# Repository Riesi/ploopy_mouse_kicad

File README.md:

# DISCLAIMER
## How was this ported to KiCAD?

The heavy lifting was done by the [altium2kicad](https://github.com/thesourcerer8/altium2kicad) converter. If you like this port do consider donating to the converter project!

After that I took the converted files and pruned unnecessary ones. Then I fixed the schematics by replacing the broken symbols with either existing ones or created custom symbols.
All components have been named as they appear in the PCB to allow for relinking of the footprints with the `Update Schematic from PCB` option in eeschema.
Finally I fixed the DRC errors generated in the PCB (default design rule settings). This meant fixing the broken edge cut lines, due to the converter creating non closed and not fully connected lines. It also sprinkled some edge cut dots over the lines, which was not that easy to find!

### Can I use this port instead of the main project?

I don't think anything speaks against using this KiCAD version. But be warned that I haven't produced a PCB with it myself! So things could be broken!
If you just want a working PCB you should use Gerber files produced from the original version instead.

If you want to help verifying the design please do so!

### Current Validation

Validation has been done with the `Gerbv` tool, which allows to compare two Gerber files and show their difference/overlap.
The files used for the validation are located in `./gerber_diff_view`. You can run the `diff_gerber.sh` to verify some of the Gerber files yourself. Be sure to generate the KiCAD Gerber in the following path `hardware/electronics/QMKMouse/gerber/` before running the script. There are also comparison shots of some layers in which the white corresponds to KiCAD, green to Altium and purple to the matching XOR of both.

#### Labels:

Text is different due to fonts.
Drawings look correct.

#### Layers:

Only minimal difference due to difference in clearance to the border cut and filling algorithm.
KiCAD version has a bit more portions filled. This should not be an issue.

#### Edge Cuts:

Match.

#### Drill:
Drill holes look correct.
Mismatch on some holes that are not plated in the fabricated PCB, but Altium files still contain them as plated.
Should be no problem.

#### Drill Maps:
No drill mapped to optical sensor in KiCAD, but this should not be an issue.

#### Masks:

Match.

#### Pastes:

Match.

# The Ploopy Mouse

By some stroke of luck, you've made your way here. The Ploopy Mouse. Your life will never be the same.

This repository contains all of the design and production files necessary to make a Ploopy Mouse. We've also included some kick-ass documentation in the Wiki on how to get it made, assemble it, and program it.

What are you waiting for? Your new life awaits.

## QMK?!

Kits bought from the [Ploopy store](https://ploopy.co/product-category/mouse/) come with QMK preloaded. Check out the Wiki for instructions on how to load new firmware onto your device. (It's super easy!)

The firmware hex file that ships with all Mice is included in this repository as well, as `ploopyco_mouse_via.hex`. The hex was built with QMK version 0.11.1.

## Under what license is this released?

Everything in this repository is released under OHL CERN v2-S. Check the LICENSE.md file for full license text.

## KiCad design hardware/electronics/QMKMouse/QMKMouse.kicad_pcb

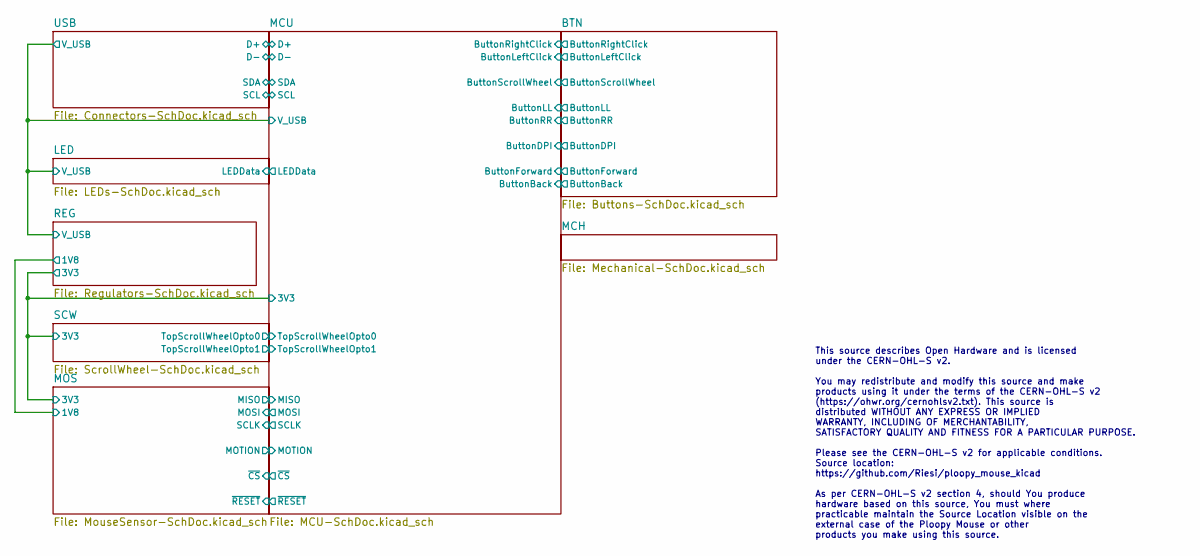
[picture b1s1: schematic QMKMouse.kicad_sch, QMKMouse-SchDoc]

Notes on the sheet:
This source describes Open Hardware and is licensed under the CERN-OHL-S v2. You may redistribute and modify this source and make products using it under the terms of the CERN-OHL-S v2 (https://ohwr.org/cernohlsv2.txt). This source is distributed WITHOUT ANY EXPRESS OR IMPLIED WARRANTY, INCLUDING O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

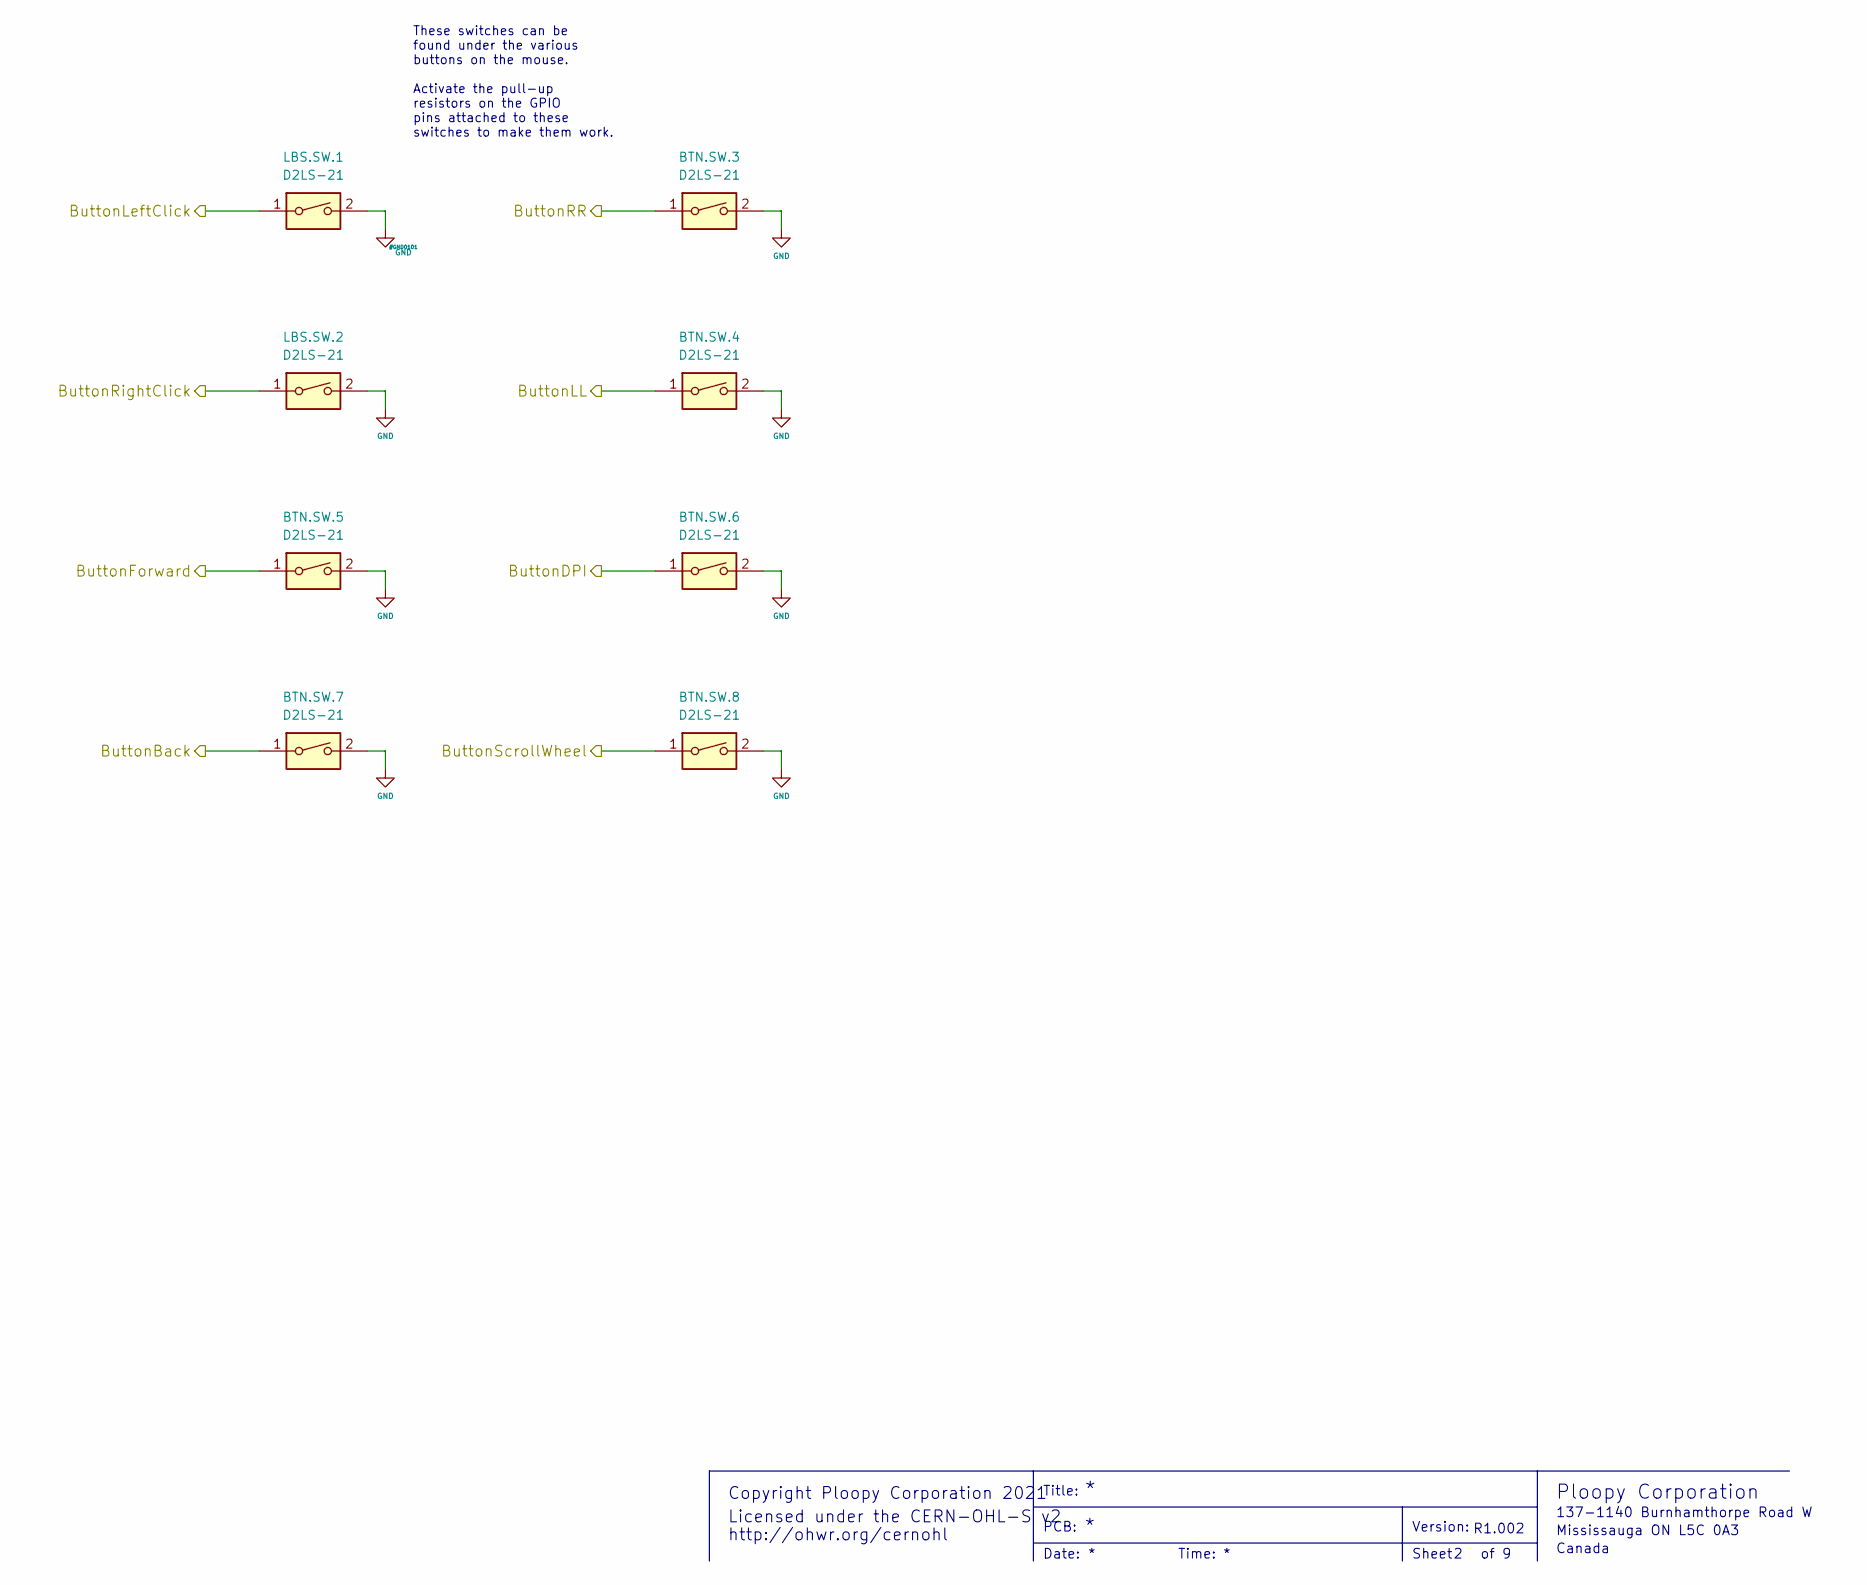
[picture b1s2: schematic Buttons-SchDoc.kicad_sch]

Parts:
BTN.SW.3, BTN.SW.4, BTN.SW.5, BTN.SW.6, BTN.SW.7, BTN.SW.8: D2LS-21
LBS.SW.1, LBS.SW.2: D2LS-21

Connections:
/BTN/ButtonBack: BTN.SW.7.1; also elsewhere on the board
/BTN/ButtonDPI: BTN.SW.6.1; also elsewhere on the board
/BTN/ButtonForward: BTN.SW.5.1; also elsewhere on the board
/BTN/ButtonLL: BTN.SW.4.1; also elsewhere on the board
/BTN/ButtonLeftClick: LBS.SW.1.1; also elsewhere on the board
/BTN/ButtonRR: BTN.SW.3.1; also elsewhere on the board
/BTN/ButtonRightClick: LBS.SW.2.1; also elsewhere on the board
/BTN/ButtonScrollWheel: BTN.SW.8.1; also elsewhere on the board
GND: BTN.SW.3.2, BTN.SW.4.2, BTN.SW.5.2, BTN.SW.6.2, BTN.SW.7.2, BTN.SW.8.2, LBS.SW.1.2, LBS.SW.2.2; also elsewhere on the board

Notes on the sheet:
Canada
PCB:
137-1140 Burnhamthorpe Road W
http://ohwr.org/cernohl
Copyright Ploopy Corporation 2021
Sheet
Title:
Mississauga ON L5C 0A3
These switches can be found under the various buttons on the mouse. Activate the pull-up resistors on the GPIO pins attached to these switches to make them work.
Version:
Ploopy Corporation
Licensed under the CERN-OHL-S v2
Time:
Date:
R1.002

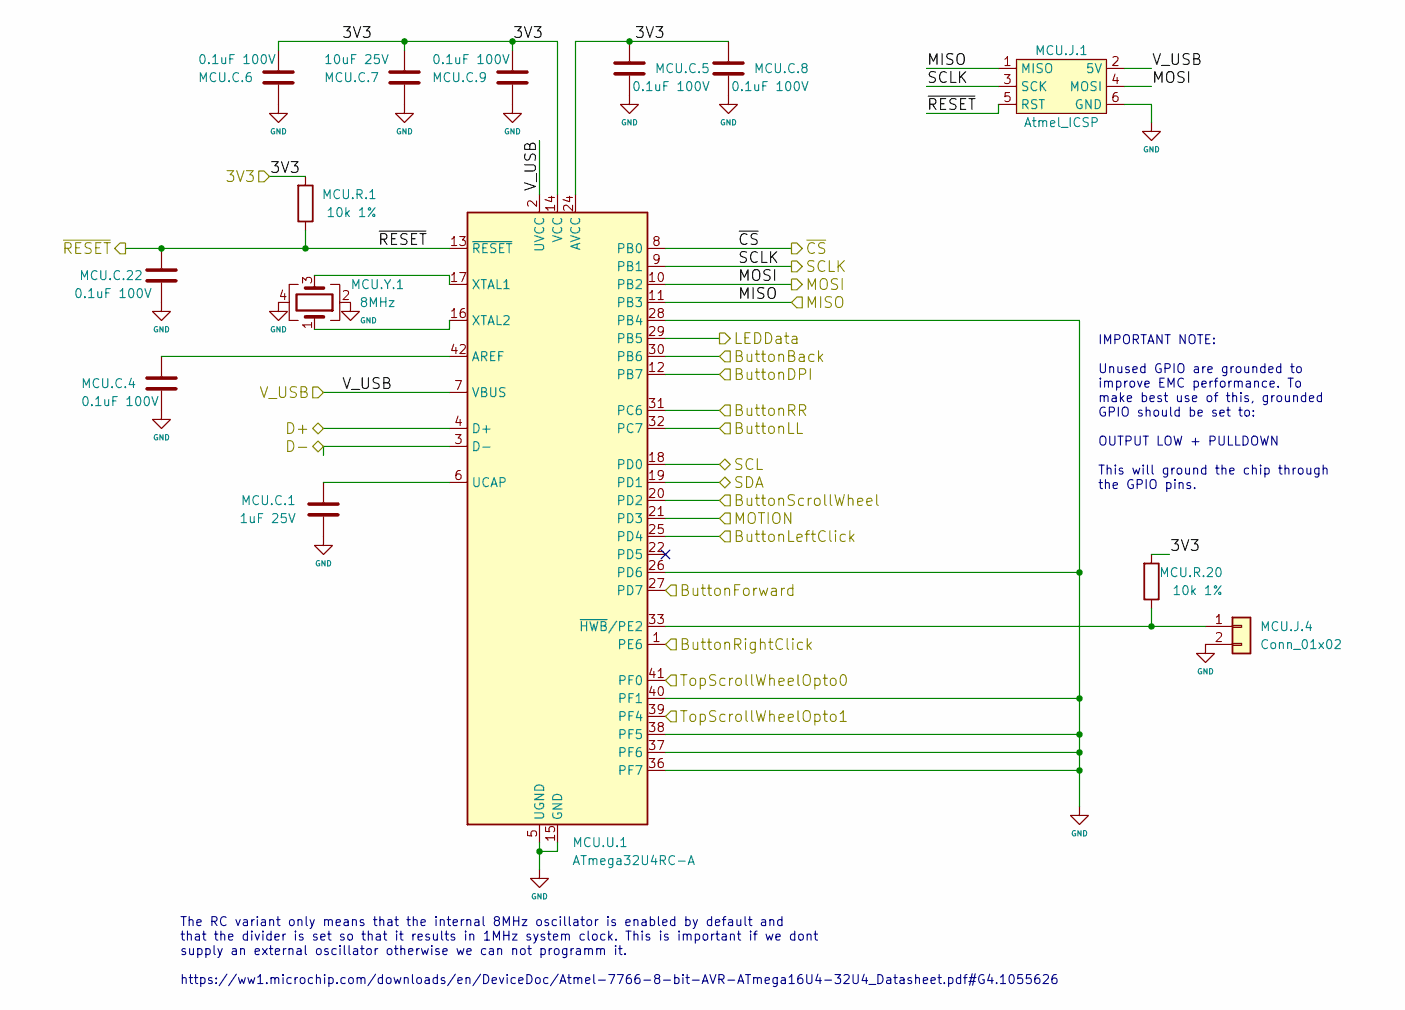
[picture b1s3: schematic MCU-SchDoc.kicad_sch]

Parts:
MCU.C.1: 1uF 25V; C_0805
MCU.C.4, MCU.C.5, MCU.C.6, MCU.C.8, MCU.C.9, MCU.C.22: 0.1uF 100V; C_0805
MCU.C.7: 10uF 25V; C_0805
MCU.J.1: Atmel_ICSP; 6x2
MCU.J.4: Conn_01x02; 2x1
MCU.R.1, MCU.R.20: 10k 1%; 0805
MCU.U.1: ATmega32U4RC-A; ATMEGA32U4 - TQFP80P1200X1200X120-44N
MCU.Y.1: 8MHz; LFXTAL055663BULK

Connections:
/BTN/ButtonBack: MCU.U.1.30 (PB6); also elsewhere on the board
/BTN/ButtonDPI: MCU.U.1.12 (PB7); also elsewhere on the board
/BTN/ButtonForward: MCU.U.1.27 (PD7); also elsewhere on the board
/BTN/ButtonLL: MCU.U.1.32 (PC7); also elsewhere on the board
/BTN/ButtonLeftClick: MCU.U.1.25 (PD4); also elsewhere on the board
/BTN/ButtonRR: MCU.U.1.31 (PC6); also elsewhere on the board
/BTN/ButtonRightClick: MCU.U.1.1 (PE6); also elsewhere on the board
/BTN/ButtonScrollWheel: MCU.U.1.20 (PD2); also elsewhere on the board
/LED/LEDData: MCU.U.1.29 (PB5); also elsewhere on the board
/LED/V_USB: MCU.J.1.2 (5V), MCU.U.1.2 (UVCC), MCU.U.1.7 (VBUS); also elsewhere on the board
/MCU/3V3: MCU.C.5.2, MCU.C.6.2, MCU.C.7.2, MCU.C.8.2, MCU.C.9.2, MCU.R.1.2, MCU.R.20.2, MCU.U.1.14 (VCC), MCU.U.1.24 (AVCC), MCU.U.1.34 (VCC), MCU.U.1.44 (AVCC); also elsewhere on the board
/MCU/D+: MCU.U.1.4 (D+); also elsewhere on the board
/MCU/D-: MCU.U.1.3 (D-); also elsewhere on the board
/MCU/MISO: MCU.J.1.1 (MISO), MCU.U.1.11 (PB3); also elsewhere on the board
/MCU/MOSI: MCU.J.1.4 (MOSI), MCU.U.1.10 (PB2); also elsewhere on the board
/MCU/MOTION: MCU.U.1.21 (PD3); also elsewhere on the board
/MCU/SCL: MCU.U.1.18 (PD0); also elsewhere on the board
/MCU/SCLK: MCU.J.1.3 (SCK), MCU.U.1.9 (PB1); also elsewhere on the board
/MCU/SDA: MCU.U.1.19 (PD1); also elsewhere on the board
/MCU/TopScrollWheelOpto0: MCU.U.1.41 (PF0); also elsewhere on the board
/MCU/TopScrollWheelOpto1: MCU.U.1.39 (PF4); also elsewhere on the board
/MCU/~CS: MCU.U.1.8 (PB0); also elsewhere on the board
/MCU/~RESET: MCU.C.22.2, MCU.J.1.5 (RST), MCU.R.1.1, MCU.U.1.13 (~RESET); also elsewhere on the board
GND: MCU.C.1.1, MCU.C.4.1, MCU.C.5.1, MCU.C.6.1, MCU.C.7.1, MCU.C.8.1, MCU.C.9.1, MCU.C.22.1, MCU.J.1.6 (GND), MCU.J.4.2, MCU.U.1.5 (UGND), MCU.U.1.15 (GND), MCU.U.1.23 (GND), MCU.U.1.26 (PD6), MCU.U.1.28 (PB4), MCU.U.1.35 (GND), MCU.U.1.36 (PF7), MCU.U.1.37 (PF6), MCU.U.1.38 (PF5), MCU.U.1.40 (PF1), MCU.U.1.43 (GND), MCU.Y.1.2, MCU.Y.1.4; also elsewhere on the board
unnamed: MCU.C.1.2, MCU.U.1.6 (UCAP)
unnamed: MCU.C.4.2, MCU.U.1.42 (AREF)
unnamed: MCU.J.4.1, MCU.R.20.1, MCU.U.1.33 (~HWB/PE2)
unnamed: MCU.U.1.16 (XTAL2), MCU.Y.1.1
unnamed: MCU.U.1.17 (XTAL1), MCU.Y.1.3

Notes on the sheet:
The RC variant only means that the internal 8MHz oscillator is enabled by default and that the divider is set so that it results in 1MHz system clock. This is important if we dont supply an external oscillator otherwise we can not programm it. https://ww1.microchip.com/downloads/en/DeviceDoc/Atmel-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
IMPORTANT NOTE: Unused GPIO are grounded to improve EMC performance. To make best use of this, grounded GPIO should be set to: OUTPUT LOW + PULLDOWN This will ground the chip through the GPIO pins.

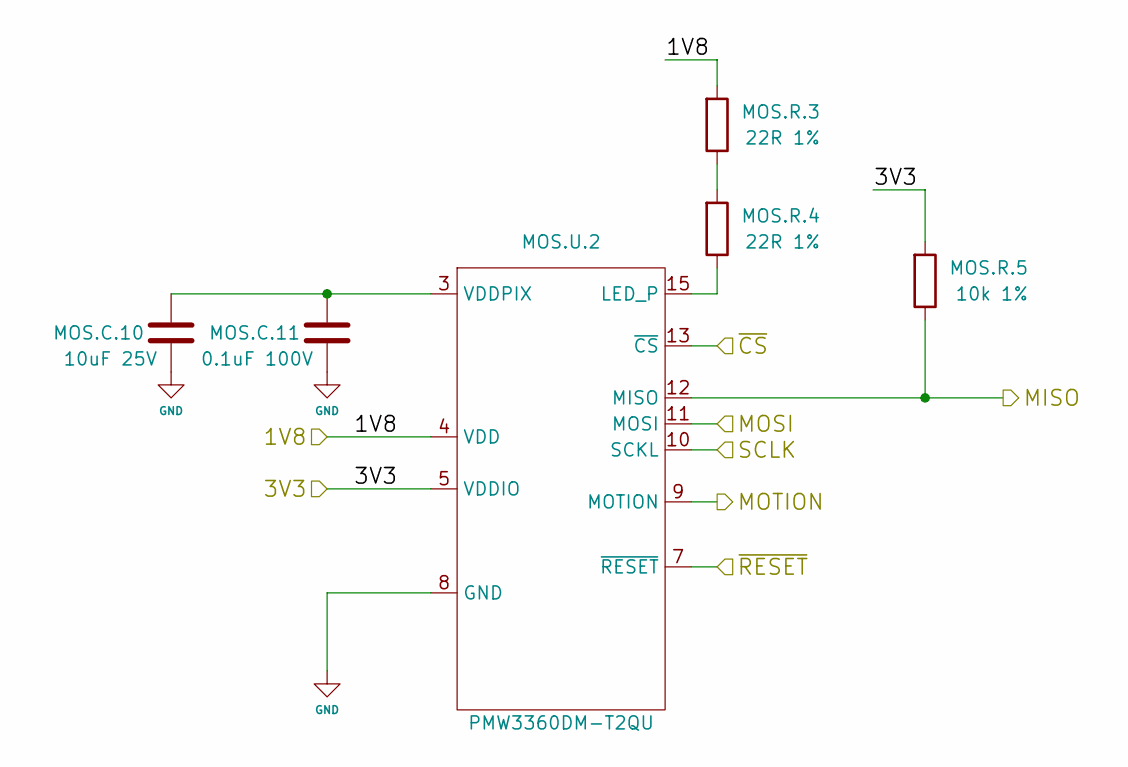
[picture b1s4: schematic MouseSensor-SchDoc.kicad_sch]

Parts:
MOS.C.10: 10uF 25V; C_0805
MOS.C.11: 0.1uF 100V; C_0805
MOS.R.3, MOS.R.4: 22R 1%; 0805
MOS.R.5: 10k 1%; 0805
MOS.U.2: PMW3360DM-T2QU

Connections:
/MCU/3V3: MOS.R.5.2, MOS.U.2.5 (VDDIO); also elsewhere on the board
/MCU/MISO: MOS.R.5.1, MOS.U.2.12 (MISO); also elsewhere on the board
/MCU/MOSI: MOS.U.2.11 (MOSI); also elsewhere on the board
/MCU/MOTION: MOS.U.2.9 (MOTION); also elsewhere on the board
/MCU/SCLK: MOS.U.2.10 (SCKL); also elsewhere on the board
/MCU/~CS: MOS.U.2.13 (~CS); also elsewhere on the board
/MCU/~RESET: MOS.U.2.7 (~RESET); also elsewhere on the board
/MOS/1V8: MOS.R.3.2, MOS.U.2.4 (VDD); also elsewhere on the board
GND: MOS.C.10.1, MOS.C.11.1, MOS.U.2.8 (GND); also elsewhere on the board
unnamed: MOS.C.10.2, MOS.C.11.2, MOS.U.2.3 (VDDPIX)
unnamed: MOS.R.3.1, MOS.R.4.2
unnamed: MOS.R.4.1, MOS.U.2.15 (LED_P)

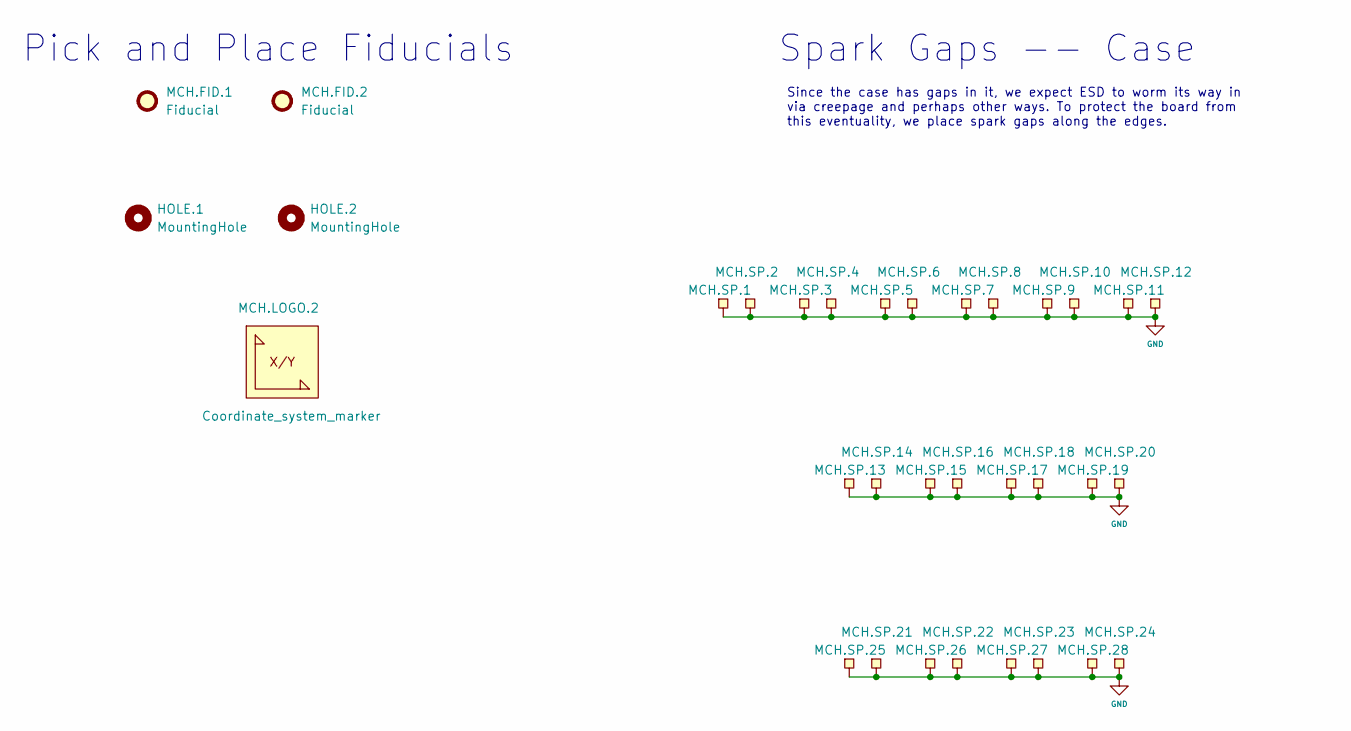
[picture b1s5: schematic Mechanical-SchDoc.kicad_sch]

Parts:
HOLE.1, HOLE.2: MountingHole
MCH.FID.1, MCH.FID.2: Fiducial; FIDUCIAL_1.5
MCH.LOGO.2: Coordinate_system_marker; Coordinate System
MCH.SP.1, MCH.SP.2, MCH.SP.3, MCH.SP.4, MCH.SP.5, MCH.SP.6, MCH.SP.7, MCH.SP.8, MCH.SP.9, MCH.SP.10, MCH.SP.11, MCH.SP.12, MCH.SP.13, MCH.SP.14, MCH.SP.15, MCH.SP.16, MCH.SP.17, MCH.SP.18, MCH.SP.19, MCH.SP.20, MCH.SP.21, MCH.SP.22, MCH.SP.23, MCH.SP.24, MCH.SP.25, MCH.SP.26, MCH.SP.27, MCH.SP.28: Spark_gap; SparkGap

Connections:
GND: MCH.SP.1.1, MCH.SP.2.1, MCH.SP.3.1, MCH.SP.4.1, MCH.SP.5.1, MCH.SP.6.1, MCH.SP.7.1, MCH.SP.8.1, MCH.SP.9.1, MCH.SP.10.1, MCH.SP.11.1, MCH.SP.12.1, MCH.SP.13.1, MCH.SP.14.1, MCH.SP.15.1, MCH.SP.16.1, MCH.SP.17.1, MCH.SP.18.1, MCH.SP.19.1, MCH.SP.20.1, MCH.SP.21.1, MCH.SP.22.1, MCH.SP.23.1, MCH.SP.24.1, MCH.SP.25.1, MCH.SP.26.1, MCH.SP.27.1, MCH.SP.28.1; also elsewhere on the board

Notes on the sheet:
Spark Gaps -- Case
Since the case has gaps in it, we expect ESD to worm its way in via creepage and perhaps other ways. To protect the board from this eventuality, we place spark gaps along the edges.
Pick and Place Fiducials

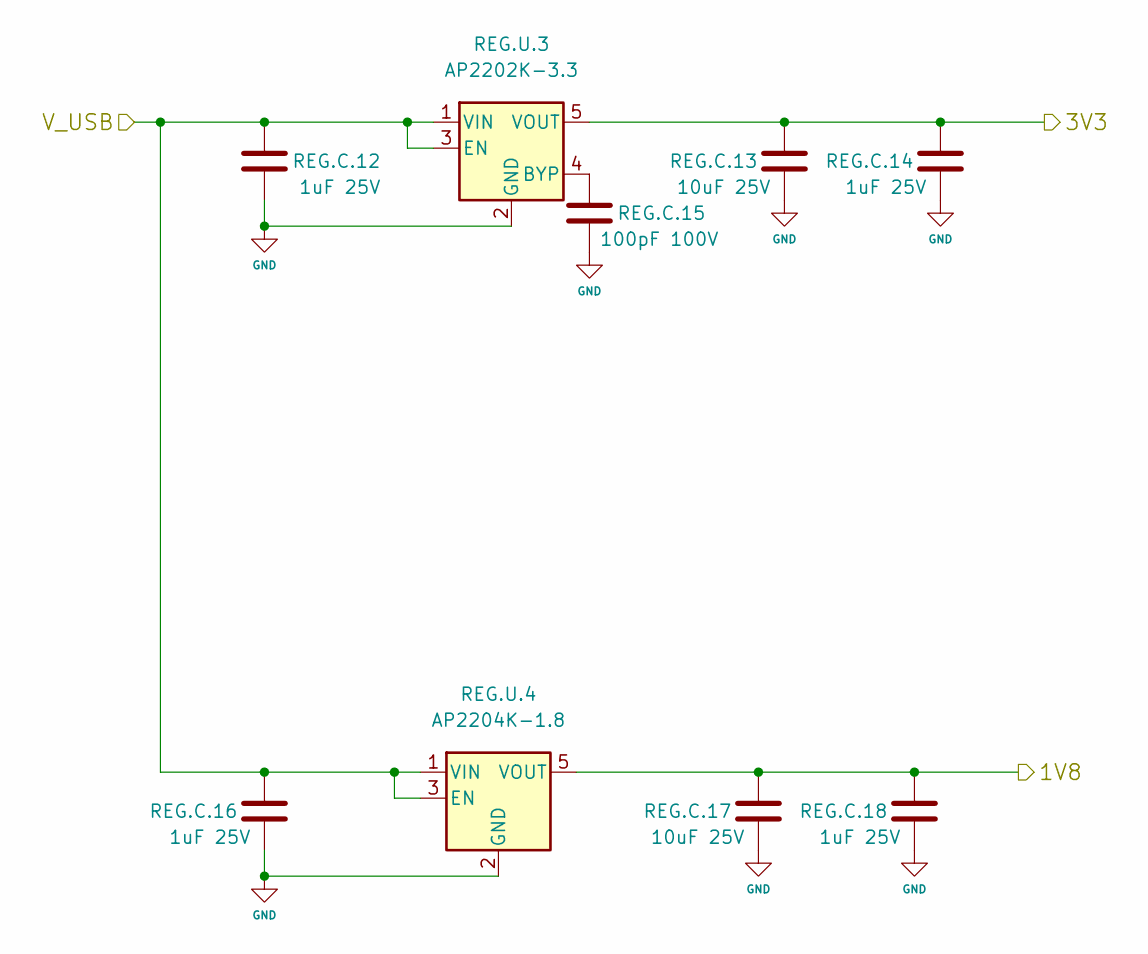
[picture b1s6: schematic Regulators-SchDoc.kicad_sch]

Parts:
REG.C.12, REG.C.14, REG.C.16, REG.C.18: 1uF 25V; C_0805
REG.C.13, REG.C.17: 10uF 25V; C_0805
REG.C.15: 100pF 100V; C_0805
REG.U.3: AP2202K-3.3; AP2202 - SOT95P270X145-5N
REG.U.4: AP2204K-1.8; AP2202 - SOT95P270X145-5N

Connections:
/LED/V_USB: REG.C.12.2, REG.C.16.2, REG.U.3.1 (VIN), REG.U.3.3 (EN), REG.U.4.1 (VIN), REG.U.4.3 (EN); also elsewhere on the board
/MCU/3V3: REG.C.13.2, REG.C.14.2, REG.U.3.5 (VOUT); also elsewhere on the board
/MOS/1V8: REG.C.17.2, REG.C.18.2, REG.U.4.5 (VOUT); also elsewhere on the board
GND: REG.C.12.1, REG.C.13.1, REG.C.14.1, REG.C.15.1, REG.C.16.1, REG.C.17.1, REG.C.18.1, REG.U.3.2 (GND), REG.U.4.2 (GND); also elsewhere on the board
unnamed: REG.C.15.2, REG.U.3.4 (BYP)

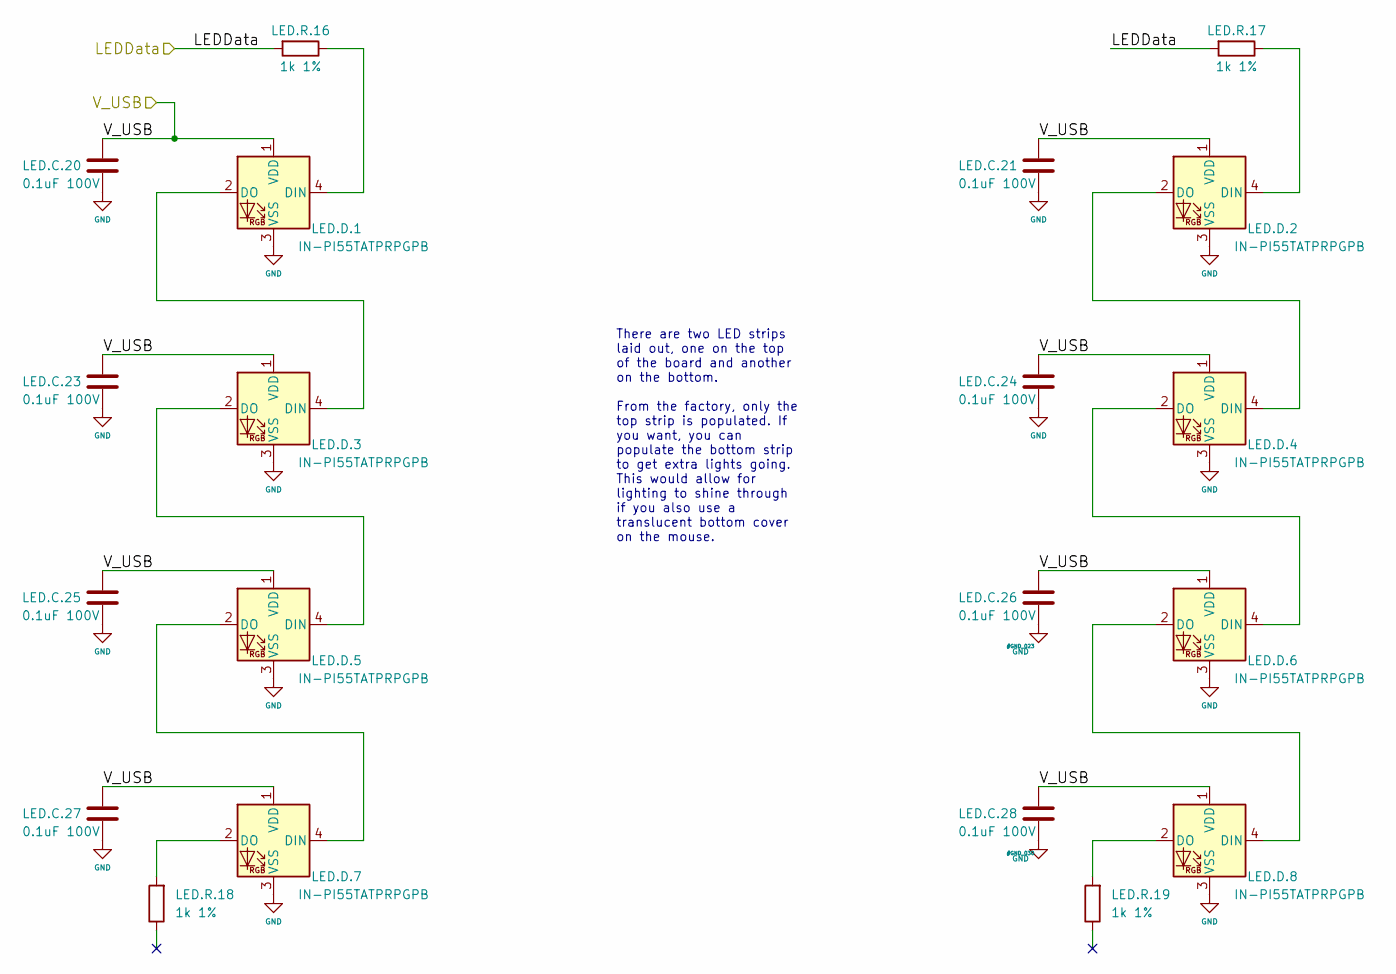
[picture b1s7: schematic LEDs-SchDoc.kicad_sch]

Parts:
LED.C.20, LED.C.21, LED.C.23, LED.C.24, LED.C.25, LED.C.26, LED.C.27, LED.C.28: 0.1uF 100V; C_0805
LED.D.1, LED.D.2, LED.D.3, LED.D.4, LED.D.5, LED.D.6, LED.D.7, LED.D.8: IN-PI55TATPRPGPB
LED.R.16, LED.R.17, LED.R.18, LED.R.19: 1k 1%; 0805

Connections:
/LED/LEDData: LED.R.16.2, LED.R.17.2; also elsewhere on the board
/LED/V_USB: LED.C.20.2, LED.C.21.2, LED.C.23.2, LED.C.24.2, LED.C.25.2, LED.C.26.2, LED.C.27.2, LED.C.28.2, LED.D.1.1 (VDD), LED.D.2.1 (VDD), LED.D.3.1 (VDD), LED.D.4.1 (VDD), LED.D.5.1 (VDD), LED.D.6.1 (VDD), LED.D.7.1 (VDD), LED.D.8.1 (VDD); also elsewhere on the board
GND: LED.C.20.1, LED.C.21.1, LED.C.23.1, LED.C.24.1, LED.C.25.1, LED.C.26.1, LED.C.27.1, LED.C.28.1, LED.D.1.3 (VSS), LED.D.2.3 (VSS), LED.D.3.3 (VSS), LED.D.4.3 (VSS), LED.D.5.3 (VSS), LED.D.6.3 (VSS), LED.D.7.3 (VSS), LED.D.8.3 (VSS); also elsewhere on the board
unnamed: LED.D.1.2 (DO), LED.D.3.4 (DIN)
unnamed: LED.D.1.4 (DIN), LED.R.16.1
unnamed: LED.D.2.2 (DO), LED.D.4.4 (DIN)
unnamed: LED.D.2.4 (DIN), LED.R.17.1
unnamed: LED.D.3.2 (DO), LED.D.5.4 (DIN)
unnamed: LED.D.4.2 (DO), LED.D.6.4 (DIN)
unnamed: LED.D.5.2 (DO), LED.D.7.4 (DIN)
unnamed: LED.D.6.2 (DO), LED.D.8.4 (DIN)
unnamed: LED.D.7.2 (DO), LED.R.18.2
unnamed: LED.D.8.2 (DO), LED.R.19.2

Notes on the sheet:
There are two LED strips laid out, one on the top of the board and another on the bottom. From the factory, only the top strip is populated. If you want, you can populate the bottom strip to get extra lights going. This would allow for lighting to shine through if you also use a translucent bottom 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

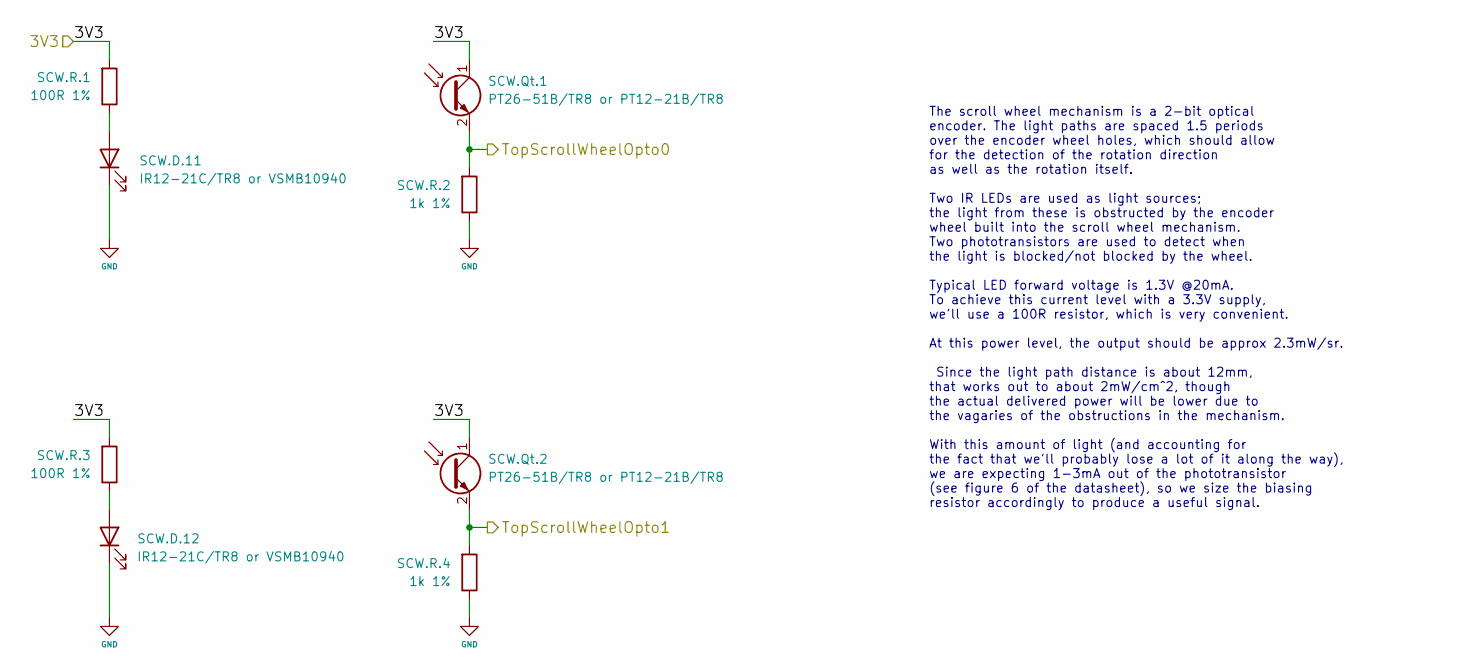
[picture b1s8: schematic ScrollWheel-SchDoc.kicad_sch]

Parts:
SCW.D.11, SCW.D.12: IR12-21C/TR8 or VSMB10940; IR12-21C-TR8
SCW.Qt.1, SCW.Qt.2: PT26-51B/TR8 or PT12-21B/TR8; PT26-51B-TR8
SCW.R.1, SCW.R.3: 100R 1%; 0805
SCW.R.2, SCW.R.4: 1k 1%; 0805

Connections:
/MCU/3V3: SCW.Qt.1.1 (C), SCW.Qt.2.1 (C), SCW.R.1.2, SCW.R.3.2; also elsewhere on the board
/MCU/TopScrollWheelOpto0: SCW.Qt.1.2 (E), SCW.R.2.2; also elsewhere on the board
/MCU/TopScrollWheelOpto1: SCW.Qt.2.2 (E), SCW.R.4.2; also elsewhere on the board
GND: SCW.D.11.1 (K), SCW.D.12.1 (K), SCW.R.2.1, SCW.R.4.1; also elsewhere on the board
unnamed: SCW.D.11.2 (A), SCW.R.1.1
unnamed: SCW.D.12.2 (A), SCW.R.3.1

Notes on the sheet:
The scroll wheel mechanism is a 2-bit optical encoder. The light paths are spaced 1.5 periods over the encoder wheel holes, which should allow for the detection of the rotation direction as well as the rotation itself. Two IR LEDs are used as light sources; the light from these is obstructed by the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

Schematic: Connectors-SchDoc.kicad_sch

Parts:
USB.C.19: 10uF 25V; C_0805
USB.FB.1, USB.FB.2, USB.FB.3, USB.FB.4, USB.FB.5: ACML-0805-601-T; 0805
USB.J.2: SJ-43514-SMT-TR
USB.J.3: DX07S016JA1R1500
USB.R.6, USB.R.7, USB.R.10, USB.R.11: 22R 1%; 0805
USB.R.8, USB.R.9, USB.R.12, USB.R.13, USB.R.14, USB.R.15: 10k 1%; 0805
USB.Z.1: IP4220CZ6; PESD3V3S4UD - SOT95P275X110-6N

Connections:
/LED/V_USB: USB.C.19.2, USB.FB.1.2; also elsewhere on the board
/MCU/D+: USB.R.7.2; also elsewhere on the board
/MCU/D-: USB.R.6.2; also elsewhere on the board
/MCU/SCL: USB.R.11.2; also elsewhere on the board
/MCU/SDA: USB.R.10.2; also elsewhere on the board
GND: USB.C.19.1, USB.J.2.4 (R2), USB.J.3.1 (GND), USB.J.3.12 (GND), USB.J.3.SHELL (SHIELD), USB.R.12.1, USB.R.13.1, USB.R.14.1, USB.R.15.1, USB.Z.1.2; also elsewhere on the board
unnamed: USB.FB.1.1, USB.J.2.1 (S), USB.J.3.2 (VBUS), USB.J.3.11 (VBUS), USB.R.8.2, USB.R.9.2, USB.Z.1.5
unnamed: USB.FB.2.1, USB.J.3.5 (D-), USB.J.3.8 (D-), USB.Z.1.3
unnamed: USB.FB.2.2, USB.R.6.1
unnamed: USB.FB.3.1, USB.J.3.6 (D+), USB.J.3.7 (D+), USB.Z.1.1
unnamed: USB.FB.3.2, USB.R.7.1
unnamed: USB.FB.4.1, USB.J.2.3 (R1), USB.R.9.1, USB.Z.1.4
unnamed: USB.FB.4.2, USB.R.10.1
unnamed: USB.FB.5.1, USB.J.2.2 (T), USB.R.8.1, USB.Z.1.6
unnamed: USB.FB.5.2, USB.R.11.1
unnamed: USB.J.3.3 (CC1), USB.R.14.2, USB.R.15.2
unnamed: USB.J.3.9 (CC2), USB.R.12.2, USB.R.13.2

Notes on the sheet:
Everyone recommends we add 10uF of capacitance to the 5V input of the USB port, so we'll do that.
Series resistors and 600Ohm ferrite beads on the I2C lines provide some protection against shorts to 5V/GND as well as ESD/EMI.
Since we hide the USB traces sandwiched between ground planes, it makes a lot of sense to make the ground planes of the PCB continuous with the cable shield.
To properly identify this device when connecting to a fully functional USB3.0 upstream device, the CC pins must be pulled down with a "5.1k" resistor. Here, 5k will do to simplify the BoM. The SBU pins in this application are unused, but perhaps in a future version they could be used to transport I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
Here we provide spaces for pull-up resistors on the I2C lines. A relatively large 10k would work well if they're not the only pull-up resistors on the bus.
This neato device protects the mouse from ESD. It should be more than adequate for this relatively tame application.

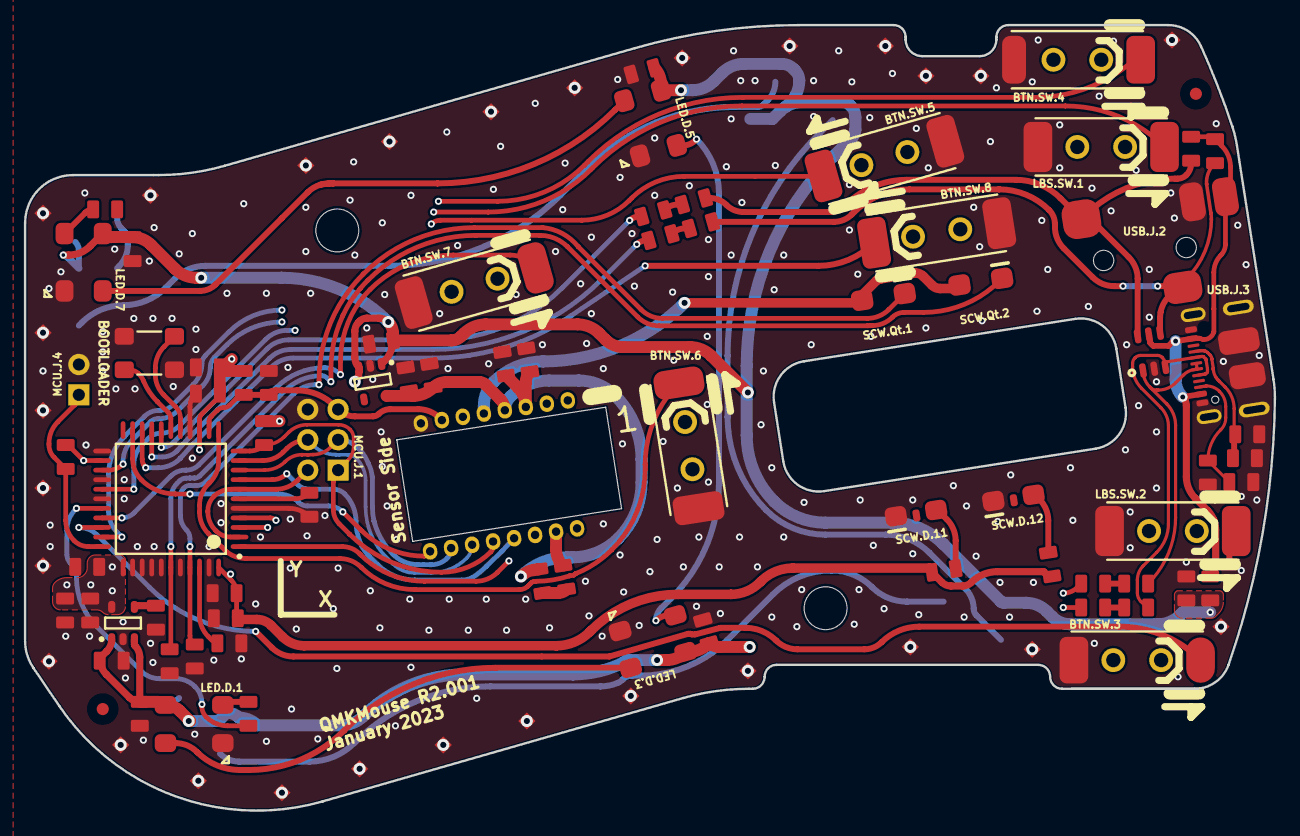
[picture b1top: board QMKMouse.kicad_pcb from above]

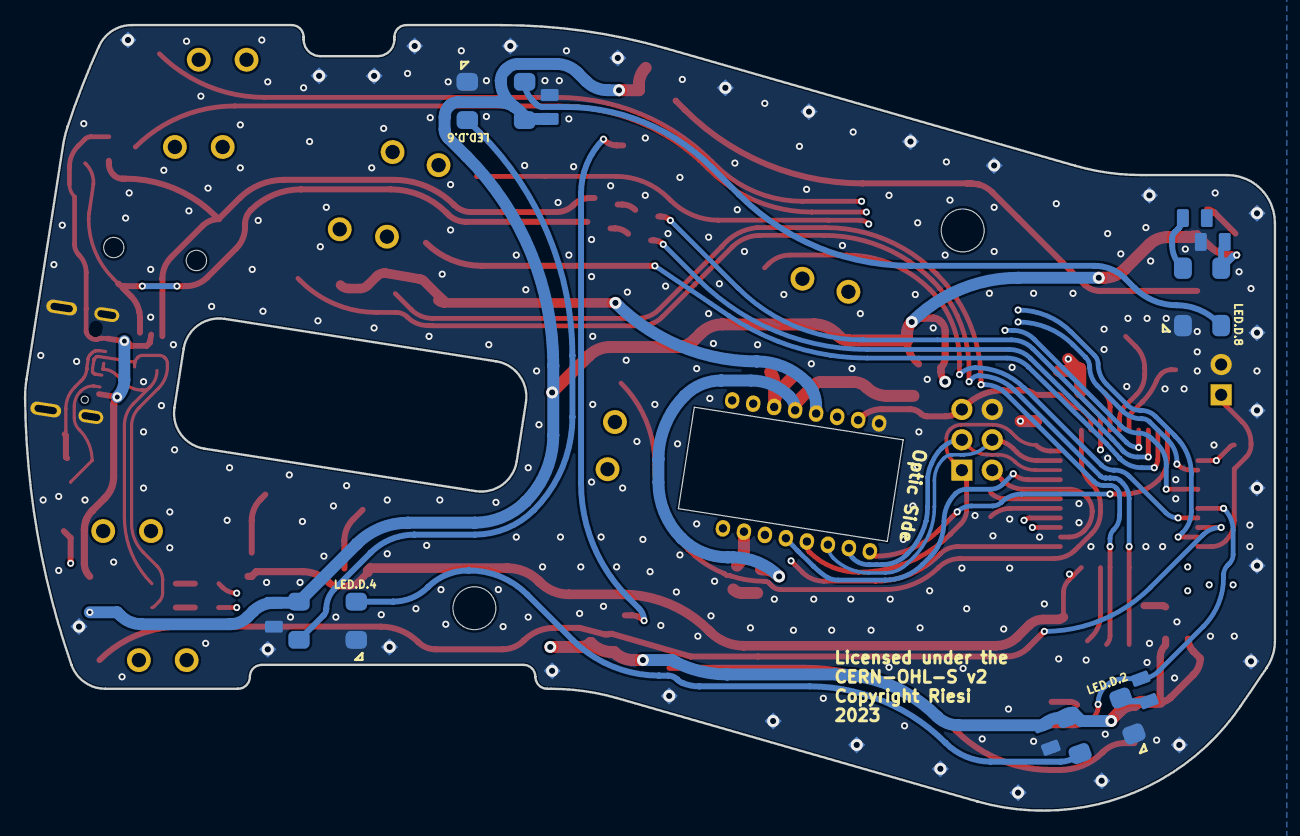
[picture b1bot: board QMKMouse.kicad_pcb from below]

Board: 4 copper layers, 104.6 x 65.8 mm, 117 parts (10 on the bottom side), 57 nets.

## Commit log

2023-01-18 Port Altium Version to KiCAD; adjust README; resize mouse image
    Here be dragons!
2023-01-19 Fix optical sensor cutout; adjust origin and PCB relative to it to match Altium to allow Gerber diffs
2023-01-19 small fix
2023-01-19 Update PCB for better matching; include some comparison Gerber files and diff images; update README
2023-01-19 improve edge cuts
2023-01-19 update schematic components
2023-01-20 change layer naming
2023-01-20 update schematic from PCB; sync netlist and fix some symbol orientations; also fix LED symbol
2023-01-20 Fix some schematic PCB mismatch
2023-01-20 Fix all remaining DRC errors and schematic mismatches
2023-01-20 update Schematic
2023-01-20 fix last sync errors
2023-01-20 fix ground connection of LED
2023-01-20 fix ERC errors and use hierarchy labels
2023-01-20 Fix all ERC errors and replot the schematic
2023-01-20 improve diff validation process
2023-01-20 fix typo in README
2023-01-20 Fix capacitor value and streamline resistor value naming
2023-01-21 fix minor Schematic naming errors; improve BoM generation
2023-01-21 correct 2 resistor values and further improve BoM (BoM matches Altium BoM now)
2023-01-23 reintroduce 3D models of some components
2023-01-23 import 0805 footprint into its own library to allow assignment of 3d model
2023-01-23 reference 3d model to all components

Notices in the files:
hardware/electronics/QMKMouse/Buttons-SchDoc.kicad_sch:
Original: Copyright Ploopy Corporation 2021
Modified: Copyright Riesi 2023
hardware/electronics/QMKMouse/QMKMouse.kicad_sch:
As per CERN-OHL-S v2 section 4, should You produce
